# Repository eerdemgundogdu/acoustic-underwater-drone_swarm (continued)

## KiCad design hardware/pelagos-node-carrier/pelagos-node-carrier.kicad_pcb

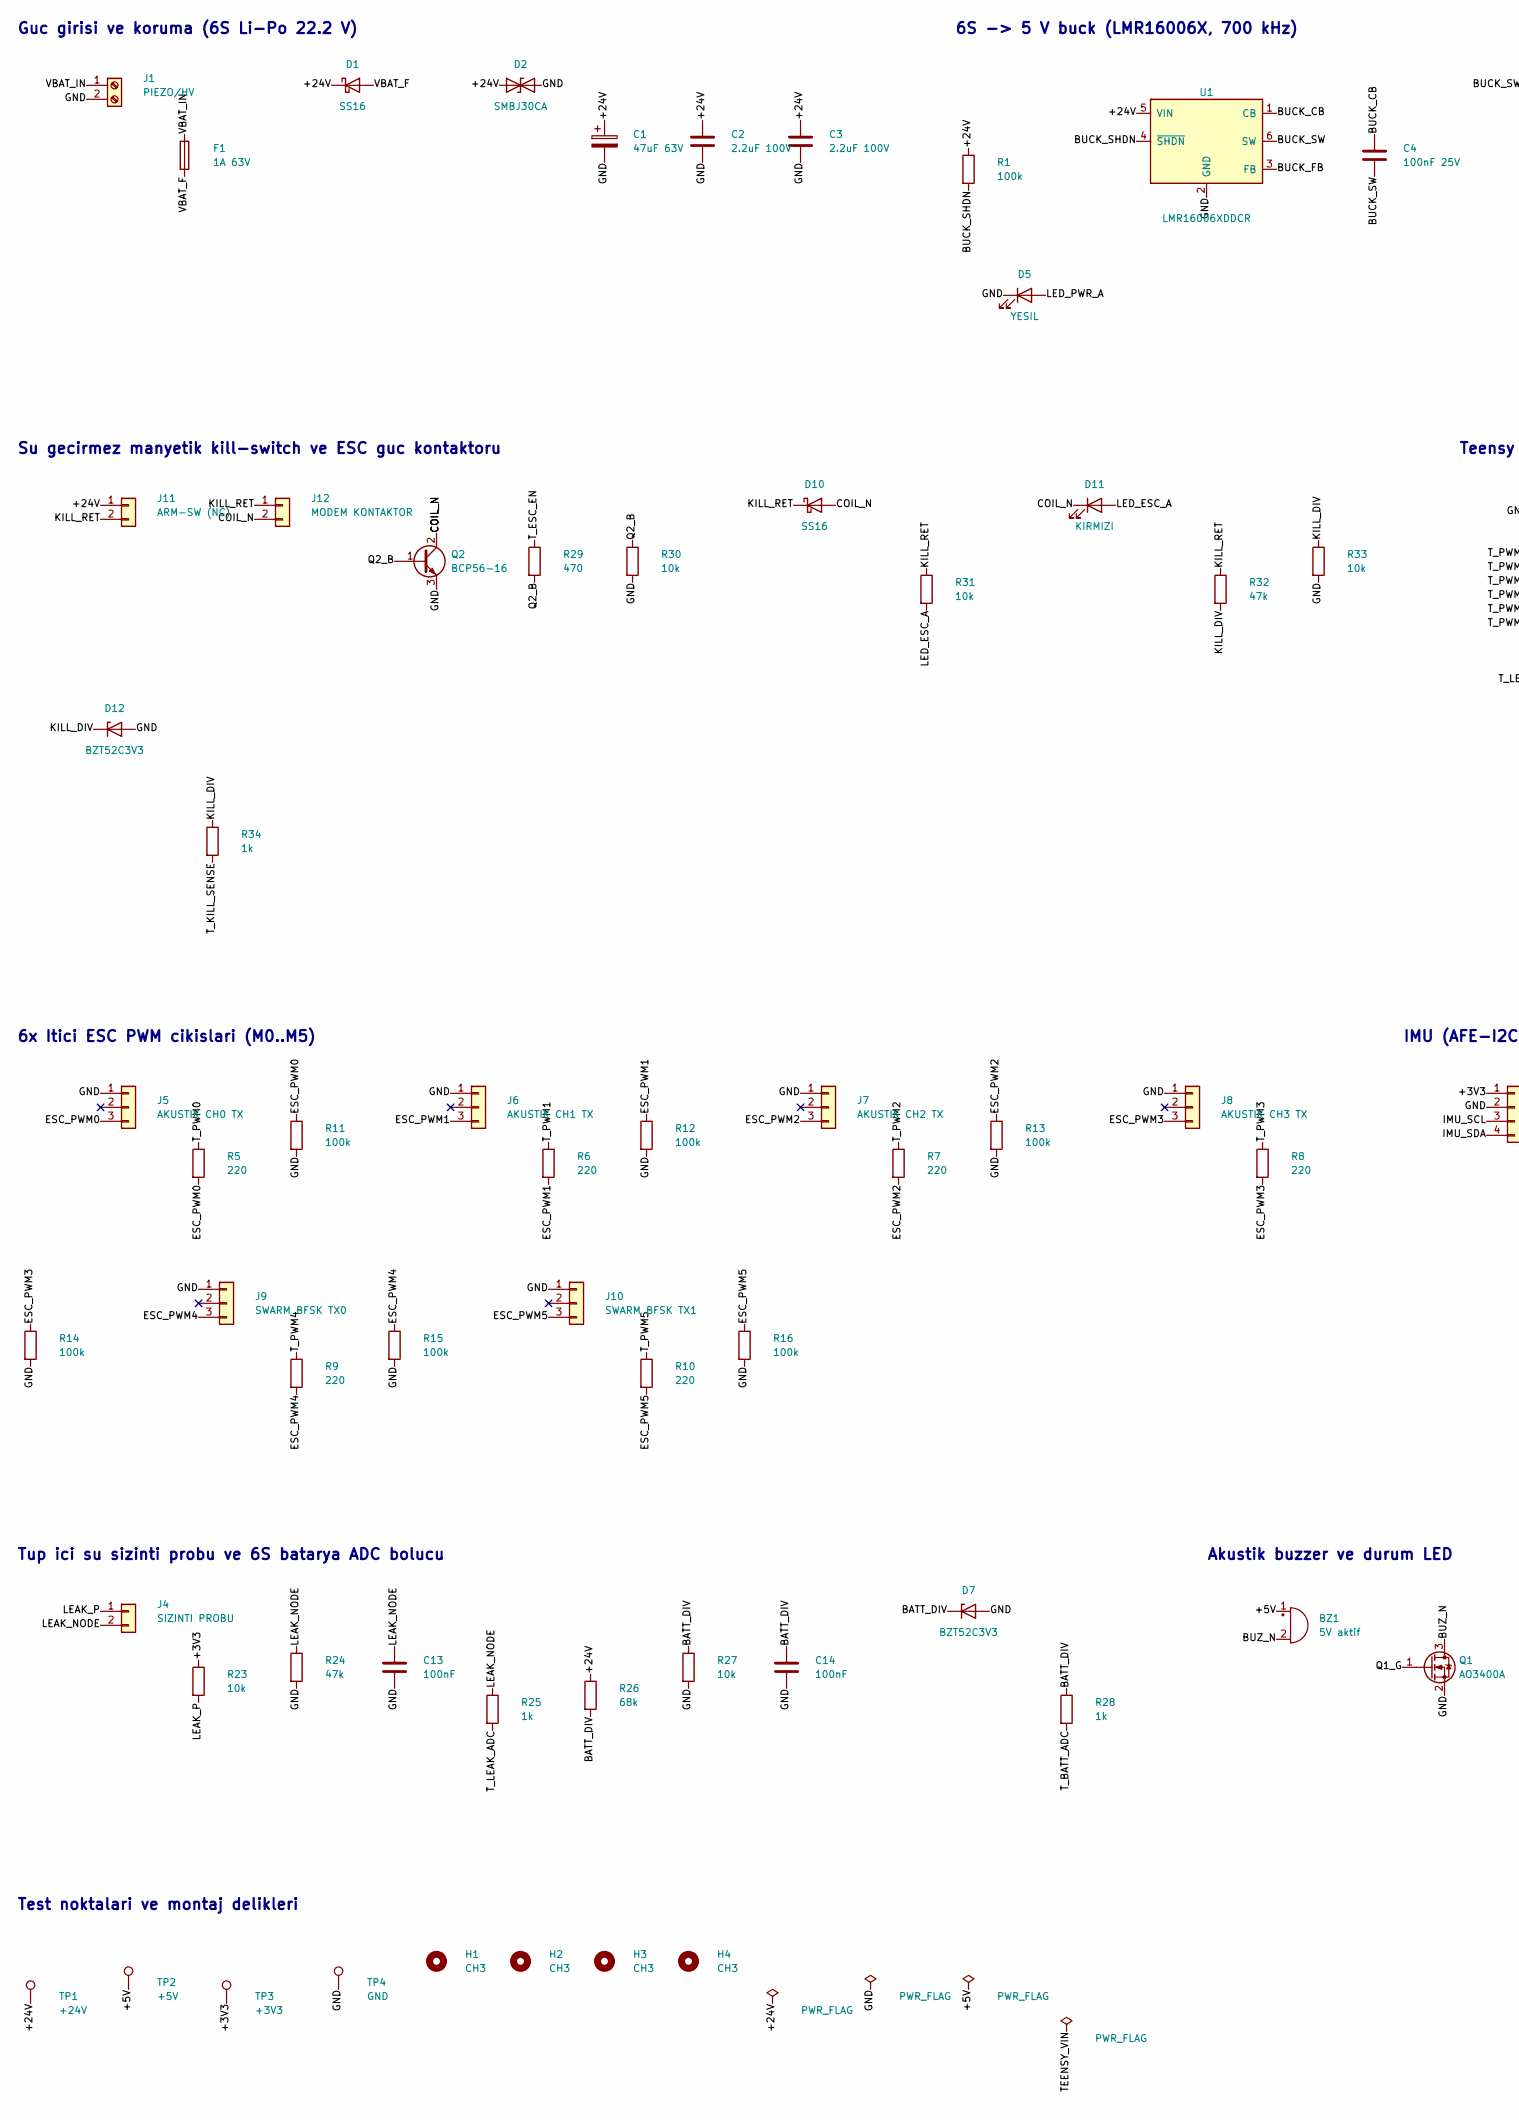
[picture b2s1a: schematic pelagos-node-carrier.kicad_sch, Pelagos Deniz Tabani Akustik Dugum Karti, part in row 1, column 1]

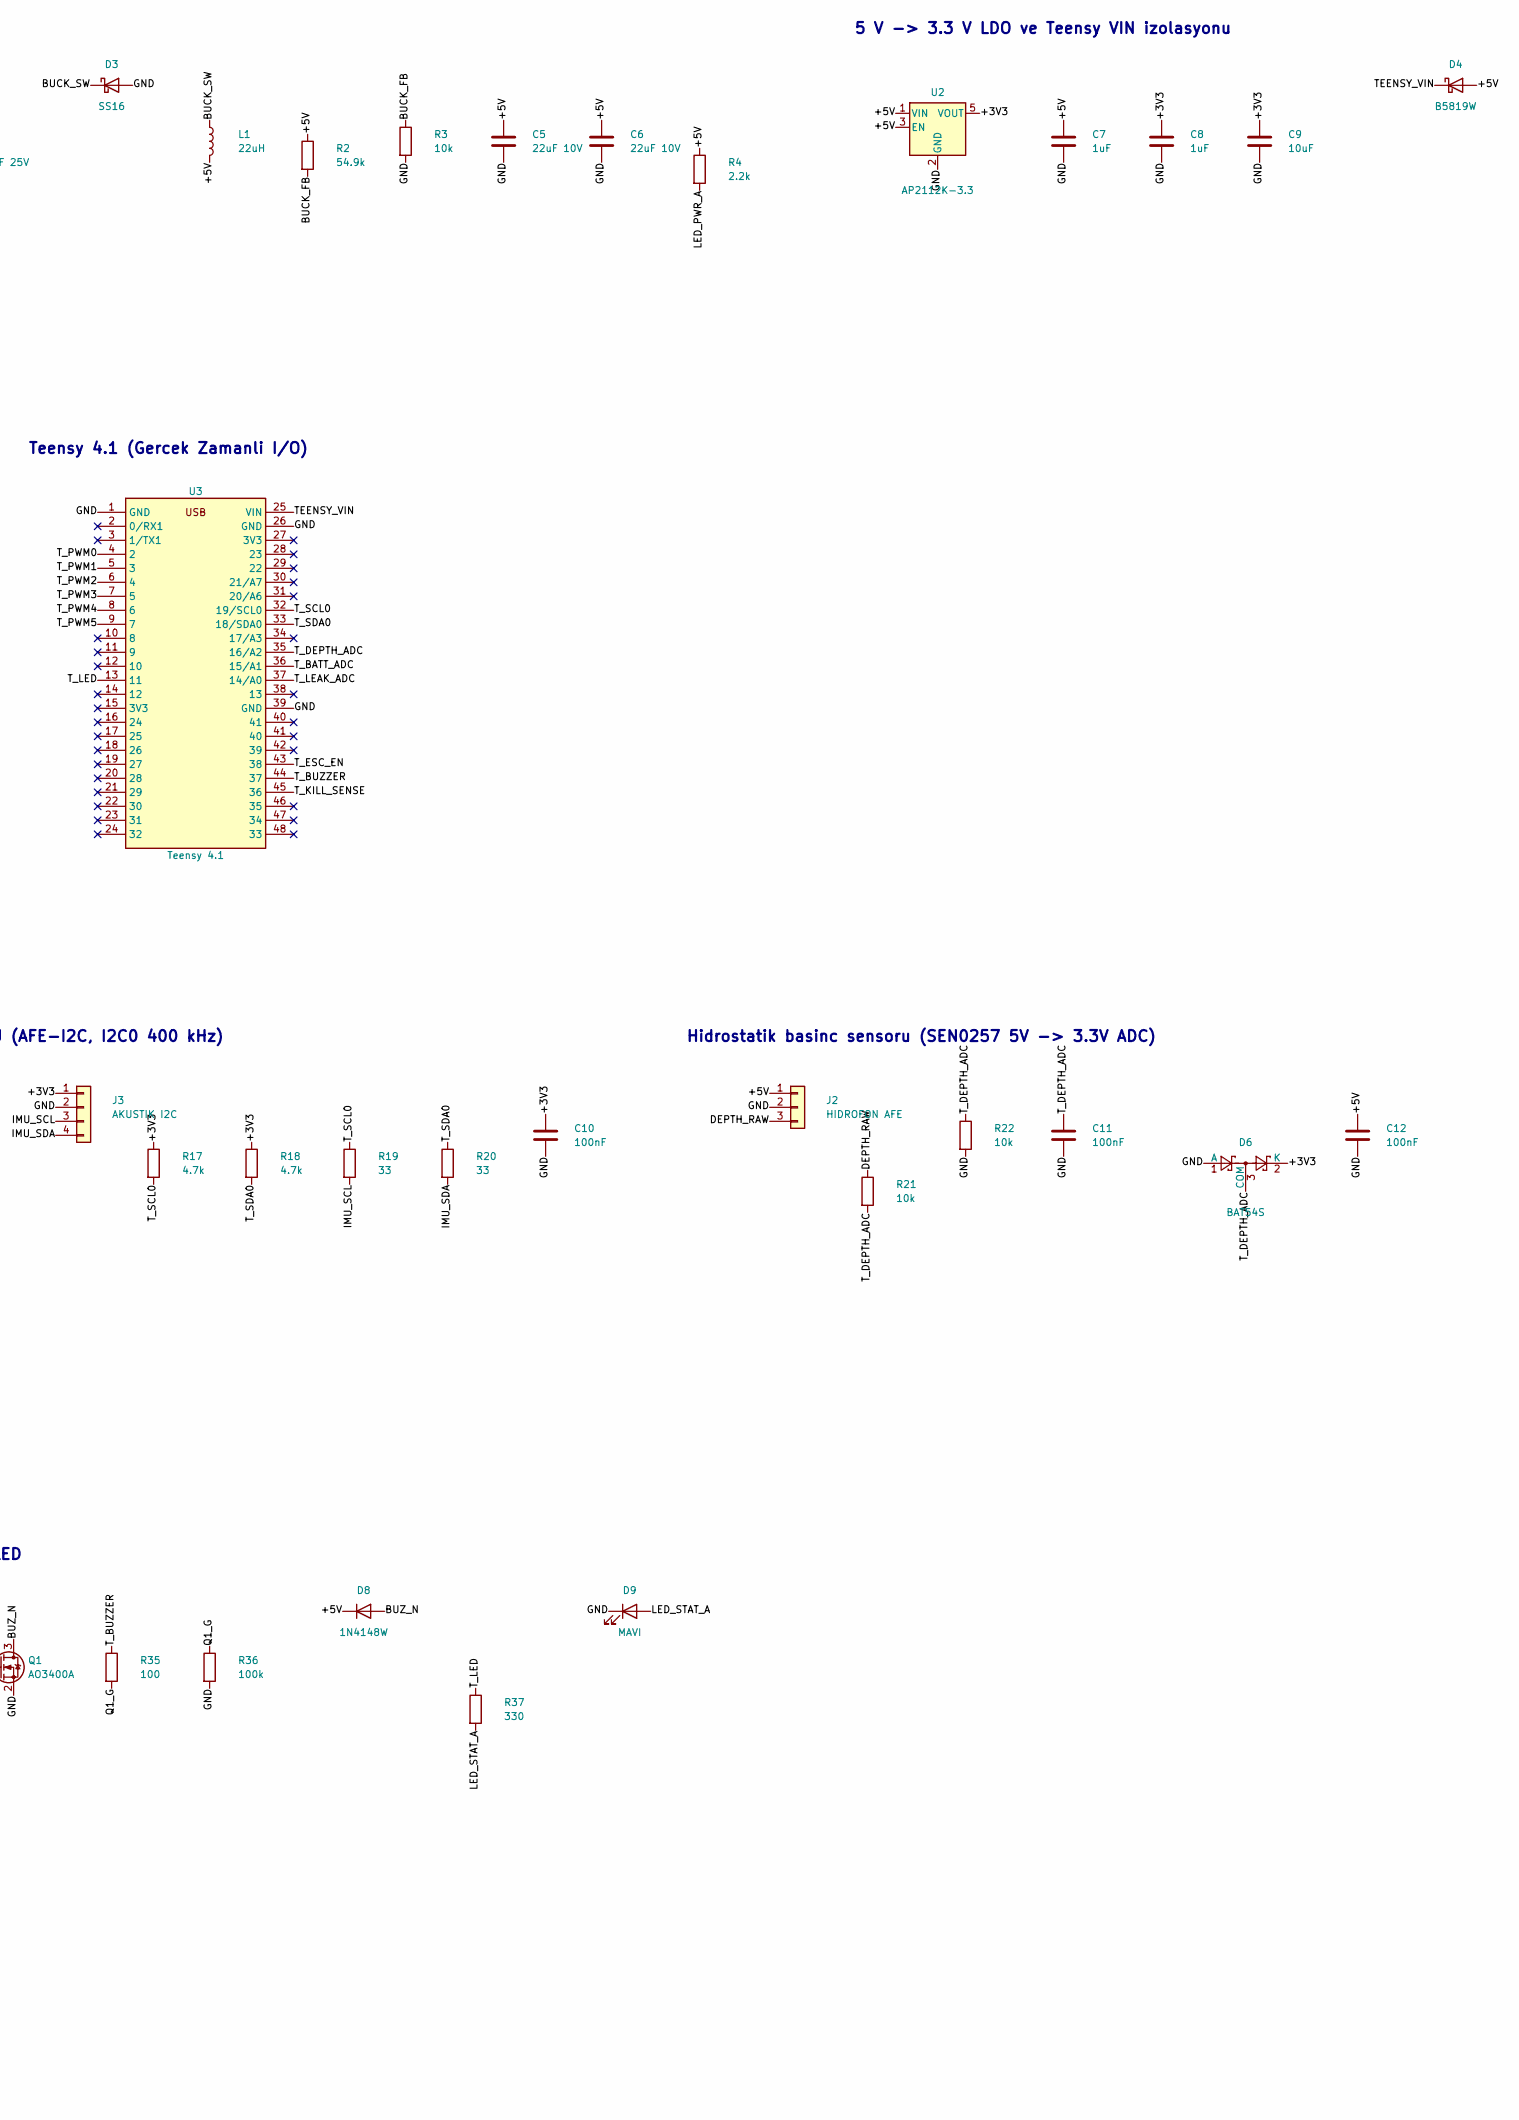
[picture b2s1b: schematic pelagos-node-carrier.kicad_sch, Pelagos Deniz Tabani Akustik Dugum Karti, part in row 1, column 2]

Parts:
BZ1: 5V aktif; Buzzer_12x9.5RM7.6; MPN 12 mm 5V aktif buzzer
C1: 47uF 63V; CP_Elec_8x10; MPN Panasonic EEE-FK1J470P
C2, C3: 2.2uF 100V; C_1210_3225Metric; MPN X7R 1210 100V
C4: 100nF 25V; C_0603_1608Metric; MPN X7R 0603 25V
C5, C6: 22uF 10V; C_1206_3216Metric; MPN X7R 1206 10V
C7, C8: 1uF; C_0603_1608Metric; MPN X7R 0603 16V
C9: 10uF; C_0805_2012Metric; MPN X5R 0805 10V
C10, C11, C12, C13, C14: 100nF; C_0603_1608Metric; MPN X7R 0603 16V
D1, D3, D10: SS16; D_SMA; MPN SS16 (60V 1A)
D2: SMBJ30CA; D_SMB; MPN Littelfuse SMBJ30CA
D4: B5819W; D_SOD-123; MPN B5819W (40V 1A)
D5: YESIL; LED_0603_1608Metric; MPN 0603 yesil LED
D6: BAT54S; SOT-23; MPN BAT54S
D7, D12: BZT52C3V3; D_SOD-123; MPN BZT52C3V3
D8: 1N4148W; D_SOD-323; MPN 1N4148WS
D9: MAVI; LED_0603_1608Metric; MPN 0603 mavi LED
D11: KIRMIZI; LED_0603_1608Metric; MPN 0603 kirmizi LED
F1: 1A 63V; Fuse_1206_3216Metric; MPN Littelfuse 0466001.NRHF
H1, H2, H3, H4: CH3; MountingHole_3.2mm_M3
J1: PIEZO/HV; TerminalBlock_Phoenix_MKDS-1,5-2-5.08_1x02_P5.08mm_Horizont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; MPN Phoenix 1715721
J2: HIDROFON AFE; JST_XH_B3B-XH-A_1x03_P2.50mm_Vertical; MPN JST B3B-XH-A
J3: AKUSTIK I2C; JST_XH_B4B-XH-A_1x04_P2.50mm_Vertical; MPN JST B4B-XH-A
J4: SIZINTI PROBU; JST_XH_B2B-XH-A_1x02_P2.50mm_Vertical; MPN JST B2B-XH-A
J5: AKUSTIK CH0 TX; JST_XH_B3B-XH-A_1x03_P2.50mm_Vertical; MPN JST B3B-XH-A
J6: AKUSTIK CH1 TX; JST_XH_B3B-XH-A_1x03_P2.50mm_Vertical; MPN JST B3B-XH-A
J7: AKUSTIK CH2 TX; JST_XH_B3B-XH-A_1x03_P2.50mm_Vertical; MPN JST B3B-XH-A
J8: AKUSTIK CH3 TX; JST_XH_B3B-XH-A_1x03_P2.50mm_Vertical; MPN JST B3B-XH-A
J9: SWARM BFSK TX0; JST_XH_B3B-XH-A_1x03_P2.50mm_Vertical; MPN JST B3B-XH-A
J10: SWARM BFSK TX1; JST_XH_B3B-XH-A_1x03_P2.50mm_Vertical; MPN JST B3B-XH-A
J11: ARM-SW (NC); JST_XH_B2B-XH-A_1x02_P2.50mm_Vertical; MPN JST B2B-XH-A
J12: MODEM KONTAKTOR; JST_XH_B2B-XH-A_1x02_P2.50mm_Vertical; MPN JST B2B-XH-A
L1: 22uH; L_Bourns_SRN6045TA; MPN Bourns SRN6045TA-220M
Q1: AO3400A; SOT-23; MPN AOS AO3400A
Q2: BCP56-16; SOT-223-3_TabPin2; MPN Nexperia BCP56-16
R1, R11, R12, R13, R14, R15, R16, R36: 100k; R_0603_1608Metric; MPN 0603 100k 1%
R2: 54.9k; R_0603_1608Metric; MPN 0603 54.9k 1%
R3, R21, R22, R23, R27, R30, R31, R33: 10k; R_0603_1608Metric; MPN 0603 10k 1%
R4: 2.2k; R_0603_1608Metric; MPN 0603 2.2k 1%
R5, R6, R7, R8, R9, R10: 220; R_0603_1608Metric; MPN 0603 220 1%
R17, R18: 4.7k; R_0603_1608Metric; MPN 0603 4.7k 1%
R19, R20: 33; R_0603_1608Metric; MPN 0603 33 1%
R24, R32: 47k; R_0603_1608Metric; MPN 0603 47k 1%
R25, R28, R34: 1k; R_0603_1608Metric; MPN 0603 1k 1%
R26: 68k; R_0603_1608Metric; MPN 0603 68k 1%
R29: 470; R_0603_1608Metric; MPN 0603 470 1%
R35: 100; R_0603_1608Metric; MPN 0603 100 1%
R37: 330; R_0603_1608Metric; MPN 0603 330 1%
TP1: +24V; TestPoint_Pad_D1.5mm
TP2: +5V; TestPoint_Pad_D1.5mm
TP3: +3V3; TestPoint_Pad_D1.5mm
TP4: GND; TestPoint_Pad_D1.5mm
U1: LMR16006XDDCR; SOT-23-6; MPN TI LMR16006XDDCR
U2: AP2112K-3.3; SOT-23-5; MPN Diodes AP2112K-3.3TRG1
U3: Teensy 4.1; Teensy4.1_Socket; MPN PJRC Teensy 4.1 + 2x 1x24 disi header

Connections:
+3V3: C8.1, C9.1, C10.1, D6.2 (K), J3.1, R17.1, R18.1, R23.1, TP3.1, U2.5 (VOUT)
+5V: BZ1.1 (+), C5.1, C6.1, C7.1, C12.1, D4.2 (A), D8.1 (K), J2.1, L1.2, R2.1, R4.1, TP2.1, U2.1 (VIN), U2.3 (EN)
+24V: C1.1, C2.1, C3.1, D1.1 (K), D2.1 (A1), J11.1, R1.1, R26.1, TP1.1, U1.5 (VIN)
BATT_DIV: C14.1, D7.1 (K), R26.2, R27.1, R28.1
BUCK_CB: C4.1, U1.1 (CB)
BUCK_FB: R2.2, R3.1, U1.3 (FB)
BUCK_SHDN: R1.2, U1.4 (~SHDN)
BUCK_SW: C4.2, D3.1 (K), L1.1, U1.6 (SW)
BUZ_N: BZ1.2 (-), D8.2 (A), Q1.3 (D)
COIL_N: D10.2 (A), D11.1 (K), J12.2, Q2.2 (C), Q2.4 (C)
DEPTH_RAW: J2.3, R21.1
ESC_PWM0: J5.3, R5.2, R11.1
ESC_PWM1: J6.3, R6.2, R12.1
ESC_PWM2: J7.3, R7.2, R13.1
ESC_PWM3: J8.3, R8.2, R14.1
ESC_PWM4: J9.3, R9.2, R15.1
ESC_PWM5: J10.3, R10.2, R16.1
GND: C1.2, C2.2, C3.2, C5.2, C6.2, C7.2, C8.2, C9.2, C10.2, C11.2, C12.2, C13.2, C14.2, D2.2 (A2), D3.2 (A), D5.1 (K), D6.1 (A), D7.2 (A), D9.1 (K), D12.2 (A), J1.2, J2.2, J3.2, J5.1, J6.1, J7.1, J8.1, J9.1, J10.1, Q1.2 (S), Q2.3 (E), R3.2, R11.2, R12.2, R13.2, R14.2, R15.2, R16.2, R22.2, R24.2, R27.2, R30.2, R33.2, R36.2, TP4.1, U1.2 (GND), U2.2 (GND), U3.1 (GND), U3.26 (GND), U3.39 (GND)
IMU_SCL: J3.3, R19.2
IMU_SDA: J3.4, R20.2
KILL_DIV: D12.1 (K), R32.2, R33.1, R34.1
KILL_RET: D10.1 (K), J11.2, J12.1, R31.1, R32.1
LEAK_NODE: C13.1, J4.2, R24.1, R25.1
LEAK_P: J4.1, R23.2
LED_ESC_A: D11.2 (A), R31.2
LED_PWR_A: D5.2 (A), R4.2
LED_STAT_A: D9.2 (A), R37.2
Q1_G: Q1.1 (G), R35.2, R36.1
Q2_B: Q2.1 (B), R29.2, R30.1
TEENSY_VIN: D4.1 (K), U3.25 (VIN)
T_BATT_ADC: R28.2, U3.36 (15/A1)
T_BUZZER: R35.1, U3.44 (37)
T_DEPTH_ADC: C11.1, D6.3 (COM), R21.2, R22.1, U3.35 (16/A2)
T_ESC_EN: R29.1, U3.43 (38)
T_KILL_SENSE: R34.2, U3.45 (36)
T_LEAK_ADC: R25.2, U3.37 (14/A0)
T_LED: R37.1, U3.13 (11)
T_PWM0: R5.1, U3.4 (2)
T_PWM1: R6.1, U3.5 (3)
T_PWM2: R7.1, U3.6 (4)
T_PWM3: R8.1, U3.7 (5)
T_PWM4: R9.1, U3.8 (6)
T_PWM5: R10.1, U3.9 (7)
T_SCL0: R17.2, R19.1, U3.32 (19/SCL0)
T_SDA0: R18.2, R20.1, U3.33 (18/SDA0)
VBAT_F: D1.2 (A), F1.2
VBAT_IN: F1.1, J1.1

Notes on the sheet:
Guc girisi ve koruma (6S Li-Po 22.2 V)
6S -> 5 V buck (LMR16006X, 700 kHz)
5 V -> 3.3 V LDO ve Teensy VIN izolasyonu
Su gecirmez manyetik kill-switch ve ESC guc kontaktoru
Teensy 4.1 (Gercek Zamanli I/O)
6x Itici ESC PWM cikislari (M0..M5)
IMU (AFE-I2C, I2C0 400 kHz)
Hidrostatik basinc sensoru (SEN0257 5V -> 3.3V ADC)
Tup ici su sizinti probu ve 6S batarya ADC bolucu
Akustik buzzer ve durum LED
Test noktalari ve montaj delikleri

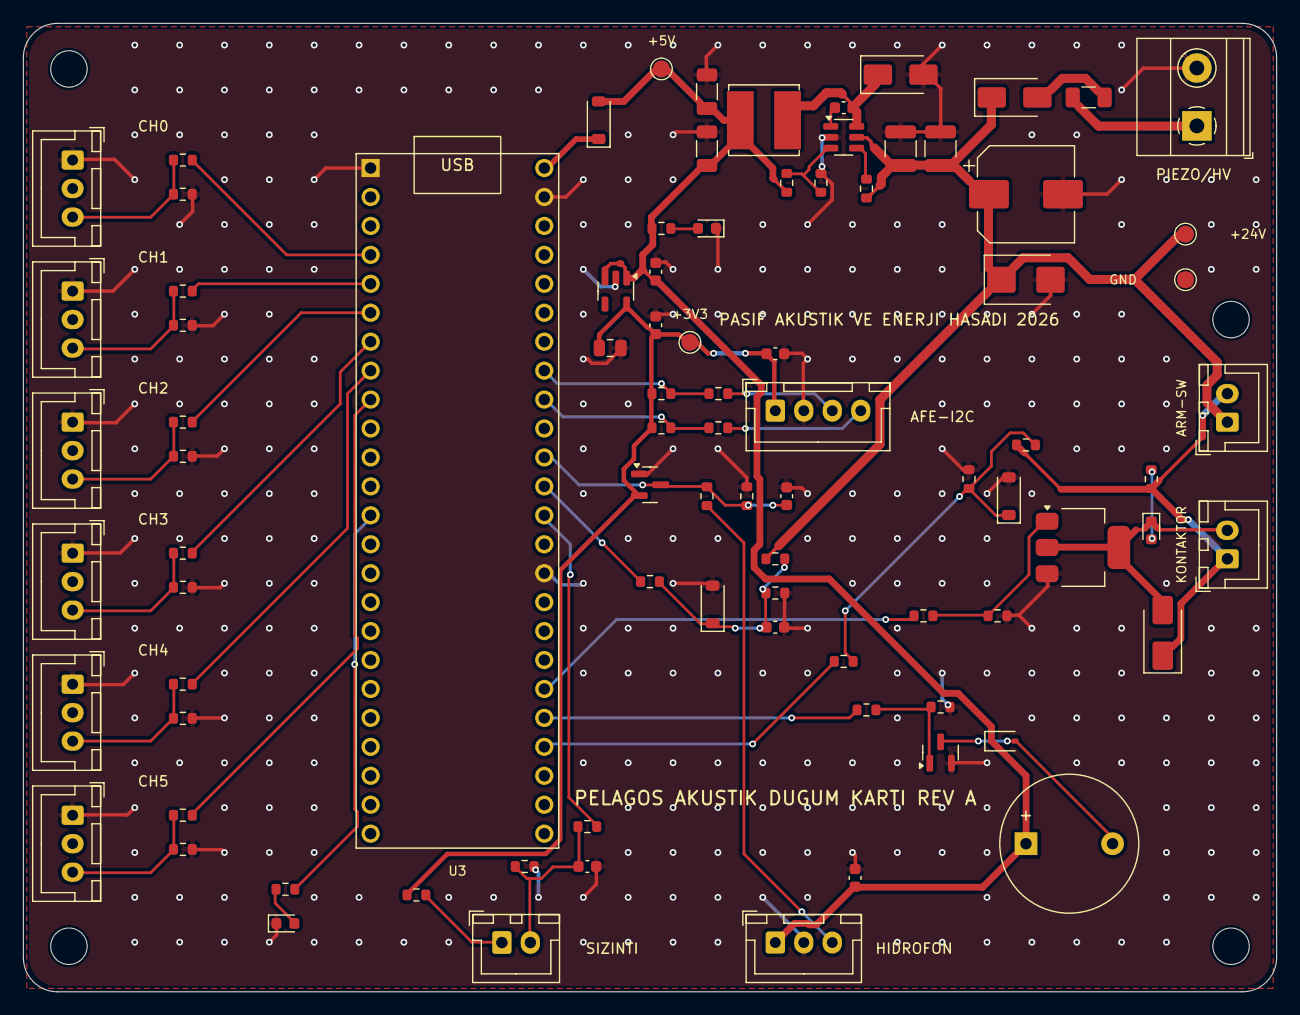
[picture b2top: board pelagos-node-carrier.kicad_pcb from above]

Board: 2 copper layers, 110.0 x 85.0 mm, 91 parts (0 on the bottom side), 47 nets.

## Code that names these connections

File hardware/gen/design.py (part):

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  VSYS      : 4S Li-ion (12.0 - 16.8 V), sigorta + manyetik kurma anahtari sonrasi
  +3V3_AON  : Hep acik alan (HT7533-1 LDO || piezo hasat LDO'su, diyot-VEYA)
              Uyanma yukselteci + karsilastirici. Uykuda toplam ~7 uA.
  +5V       : LMR16006X buck; EN pini uyanma mandali (BUCK_EN) ile surulur.
              Uykuda kapali -> Teensy, AFE ve modem enerjisiz.
  +3V3A     : LP5907 dusuk gurultulu LDO, sadece hidrofon AFE icin.

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R('R35', '100', 'AFE_LO', 'T_ADC_LO', B)
C('C36', '2.2nF', 'T_ADC_LO', 'GND', B, mpn='C0G 0603 50V')
add('D11', 'Diode:BAT54S', 'BAT54S', SOT23,
    {'1': 'GND', '2': '+3V3A', '3': 'T_ADC_LO'}, 'BAT54S', 'Pin 16 (A2) kiskaci', B)
R('R36', '100', 'AFE_HI', 'T_ADC_HI', B)
C('C37', '2.2nF', 'T_ADC_HI', 'GND', B, mpn='C0G 0603 50V')
add('D12', 'Diode:BAT54S', 'BAT54S', SOT23,
    {'1': 'GND', '2': '+3V3A', '3': 'T_ADC_HI'}, 'BAT54S', 'Pin 17 (A3) kiskaci', B)

# =============================================================================
# 10. Akustik modem vericisi: DRV8871 H-koprusu, 24/28 kHz BFSK
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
